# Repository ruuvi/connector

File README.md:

# Ruuvi Connector system

Ruuvi Connector is a standardised expansion connector and cable system that takes sensor prototyping to the next level. Compatible connectors will be found on many upcoming Ruuvi products.

There are many ways on how to use the Ruuvi Connector system:

1) Connect compatible external boards and sensors to your Ruuvi products
2) Design your own Ruuvi Connector expansion boards
3) Feed your battery powered Ruuvi products from external power sources
4) Add a Ruuvi Connector compatible connector on your own product and make it compatible with all the external Ruuvi / Grove / Qwiic / STEMMA / Gravity sensors
5) Innovate and create something totally new

Ruuvi Connector is compatible with 4-pin (2 signals + VDD + GND) prototyping systems such as [Seeed Studio Grove](http://wiki.seeedstudio.com/Grove_System/), [Sparkfun Qwiic](https://www.sparkfun.com/qwiic), [Adafruit STEMMA](https://learn.adafruit.com/introducing-adafruit-stemma-qt/), [DFRobot Gravity](https://www.dfrobot.com/gravity) and more.

## Ruuvi Connector pin-out

Ruuvi Connector cables have 8 pins (6 signals + VDD + GND). This allows using not just simple I2C sensors but also more powerful SPI sensors equipped with interrupt signals.

Note that on RuuviTags that have Ruuvi Connectors available, pins 2 and 3 are shared with internal I2C sensors. Also pin 7 is connected to TMP117 temperature sensor's interrupt signal (if a TMP117 is populated) but because the interrupt pin is an open-drain output and because it's not active in the Ruuvi firmware by default, it doesn't reserve the pin and it can be safely used for other purposes as long as TMP117 isn't configured to pull it down.

1) VDD (1.8V - 3.6V, default = 3.3V)
2) I2C_SCL / UART_RXD / ADC / GPIO
3) I2C_SDA / UART_TXD / ADC / GPIO
4) SPI_MISO / ADC / GPIO
5) SPI_MOSI / ADC / GPIO
6) SPI_SCK / ADC / GPIO
7) SPI_CS / ADC / GPIO
8) GND

Default FPC connector is [AFC07-S08ECA-00](https://lcsc.com/product-detail/Others_JUSHUO-AFC07-S08ECA-00_C262581.html).
## Dimensions of expansion boards 

1) 17.5 x 40 mm (17.5 x 25 mm without mounting holes). Used on the breakout board. 
2) 11 x 25 mm. Used on the external temperature sensor board.
3) TBD

## License

All the design files in this repository are licensed using Attribution-ShareAlike 4.0 International (CC BY-SA 4.0). Copyright: Ruuvi Innovations Ltd (Oy). Neither the name of the Ruuvi nor the names of its contributors may be used to endorse or promote products derived from this project without a specific prior written permission. While unofficial products should not have "Ruuvi" in their name, it's okay to describe your product in relation to the Ruuvi projects. More info: license@ruuvi.com.

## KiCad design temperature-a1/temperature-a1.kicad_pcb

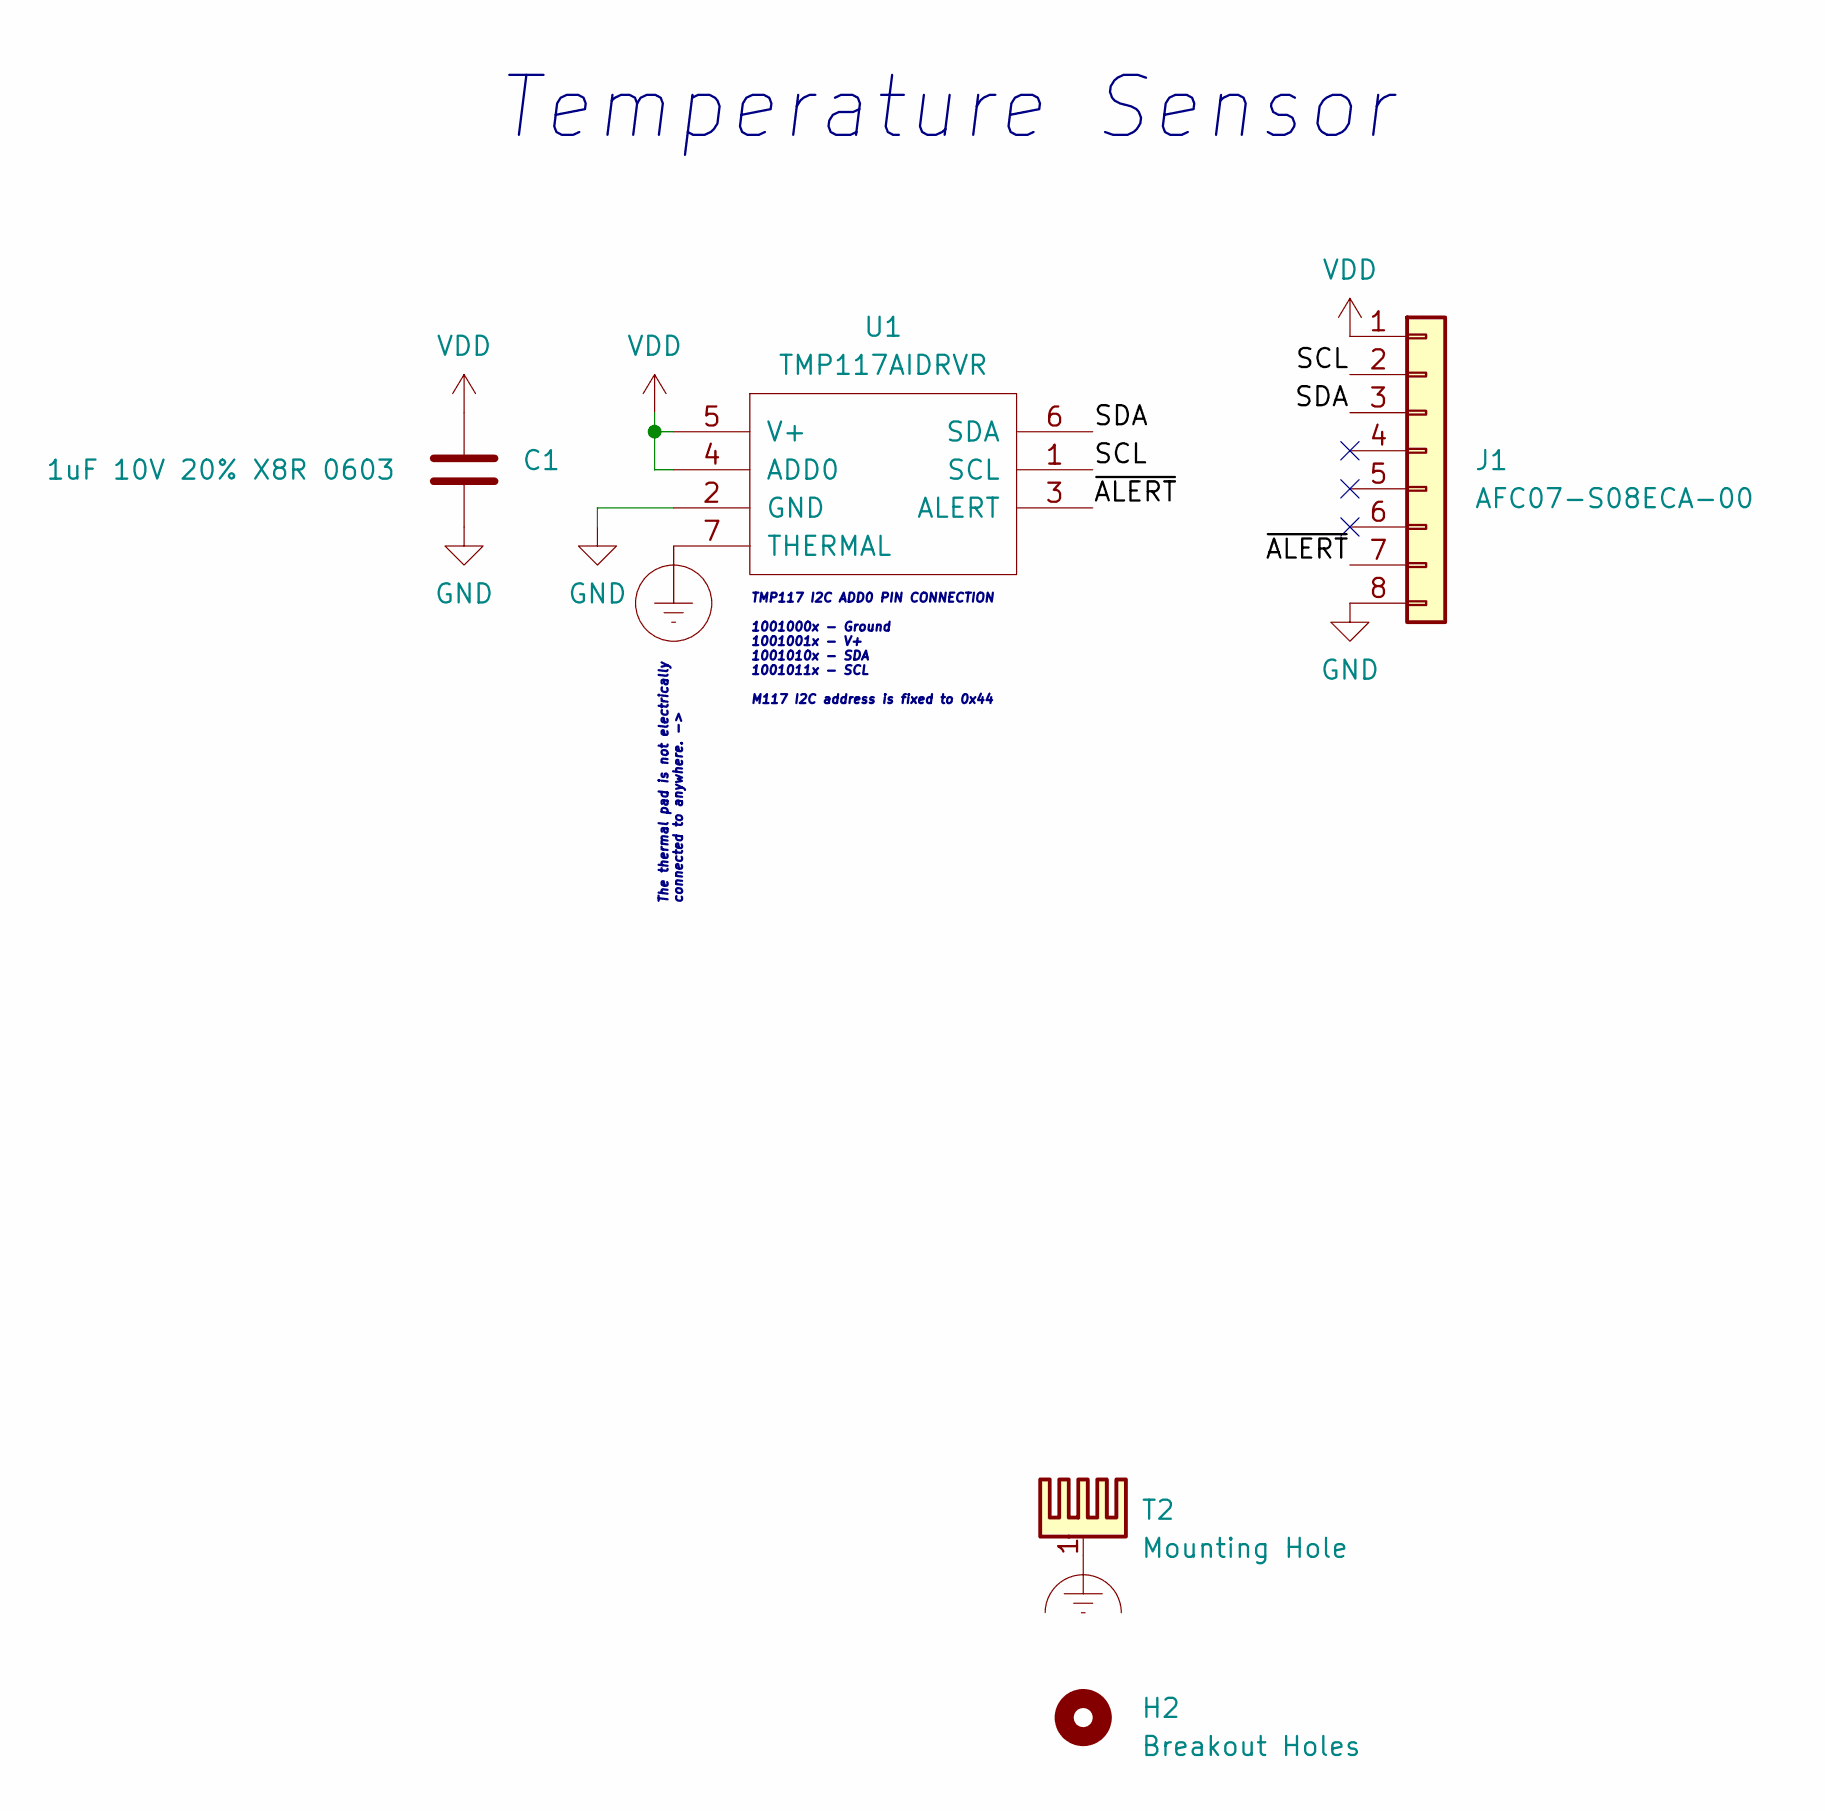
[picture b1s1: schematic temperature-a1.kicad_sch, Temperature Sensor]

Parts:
C1: 1uF 10V 20% X8R 0603; 0603_CAP
H2: Breakout Holes; BreakoutHoles
J1: AFC07-S08ECA-00; RUUVI_CONNECTOR_FFC
T2: Mounting Hole; MountingHole_3.2mm_M3_Pad_Via
U1: TMP117AIDRVR; WSON6

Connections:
/SCL: J1.2, U1.1 (SCL)
/SDA: J1.3, U1.6 (SDA)
/~ALERT: J1.7, U1.3 (ALERT)
Earth_Clean: T2.1
Earth_Protective: U1.7 (THERMAL)
GND: C1.2, J1.8, U1.2 (GND)
VDD: C1.1, J1.1, U1.4 (ADD0), U1.5 (V+)

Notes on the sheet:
The thermal pad is not electrically connected to anywhere. ->
TMP117 I2C ADD0 PIN CONNECTION 1001000x - Ground 1001001x - V+ 1001010x - SDA 1001011x - SCL M117 I2C address is fixed to 0x44
Temperature Sensor

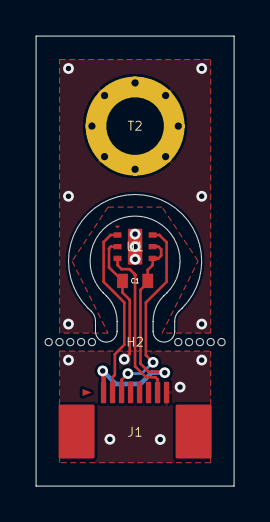
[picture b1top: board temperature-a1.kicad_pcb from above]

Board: 2 copper layers, 11.0 x 25.0 mm, 5 parts (0 on the bottom side), 5 nets.

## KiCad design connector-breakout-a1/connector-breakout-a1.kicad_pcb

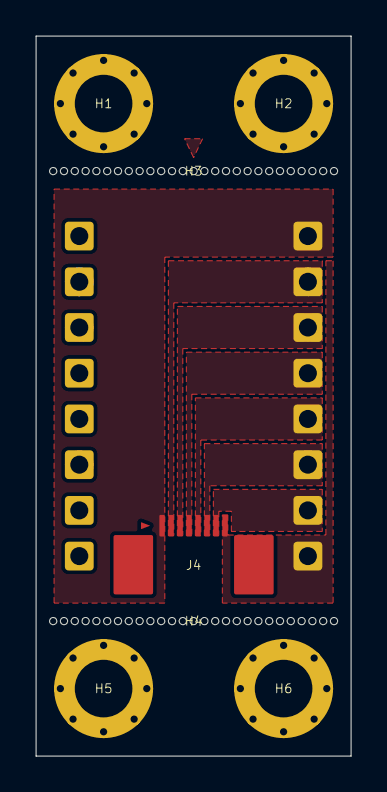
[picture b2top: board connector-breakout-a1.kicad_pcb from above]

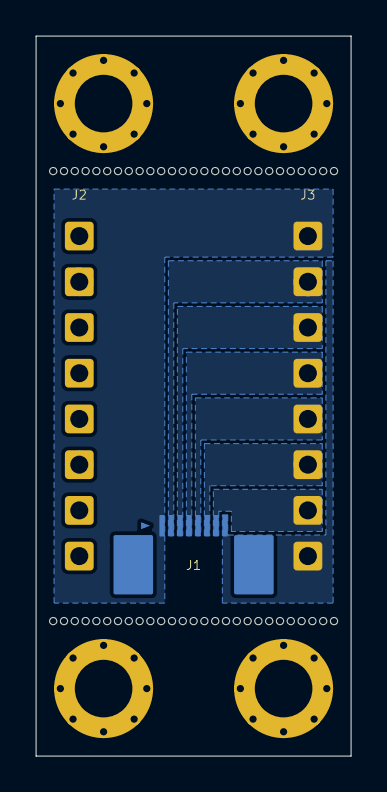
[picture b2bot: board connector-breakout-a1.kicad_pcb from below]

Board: 2 copper layers, 17.5 x 40.0 mm, 10 parts (3 on the bottom side), 16 nets.

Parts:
H1, H2, H5, H6: MountingHole; MountingHole_3.2mm_M3_Pad_Via
H3, H4: 27 x 0.4mm NPTH; BreakoutHoles
J1, J4: Ruuvi Connector Horizontal; RUUVI_CONNECTOR_FFC
J2, J3: Ruuvi Connector Pin Header; RUUVI_CONNECTOR_8PIN_HEADER

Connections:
unnamed: J1.1, J3.1
unnamed: J1.2, J3.2
unnamed: J1.3, J3.3
unnamed: J1.4, J3.4
unnamed: J1.5, J3.5
unnamed: J1.6, J3.6
unnamed: J1.7, J3.7
unnamed: J1.8, J3.8
unnamed: J2.1, J4.1
unnamed: J2.2, J4.2
unnamed: J2.3, J4.3
unnamed: J2.4, J4.4
unnamed: J2.5, J4.5
unnamed: J2.6, J4.6
unnamed: J2.7, J4.7
unnamed: J2.8, J4.8

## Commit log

2019-07-11 Add images
2020-02-15 Add Breakout A1
2020-03-01 Create BOM and component positioning file
2020-04-10 Add gitignore, remove DS_Store file
2020-04-10 Add license info
2020-05-19 Add FPC Connector model of breakout board.
    Fixes #4.
2021-03-28 New project template using the latest Kicad nightly build 20210228
2021-03-28 Extend the gitignore
2021-03-28 Add a lib, initialise, no content yet
2021-03-28 Update lib path and type
2021-03-28 Add TMP117, connector, pull-ups and a bypass cap
2021-03-29 First revision, drc pass
2021-03-29 Save
2021-04-02 Add BOM
2021-04-02 Add component positioning file
2021-04-02 Add readme
2021-04-02 Export gerbers
2021-04-02 Several minor updates and layout polishing
2021-04-02 Modify panel size
2021-06-23 Major pinout update to clarify usage with RuuviTags that have shared I2C
